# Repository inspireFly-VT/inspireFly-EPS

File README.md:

# inspireFly-EPS
inspireFly's custom EPS made for development of an open CubeSat architecture.

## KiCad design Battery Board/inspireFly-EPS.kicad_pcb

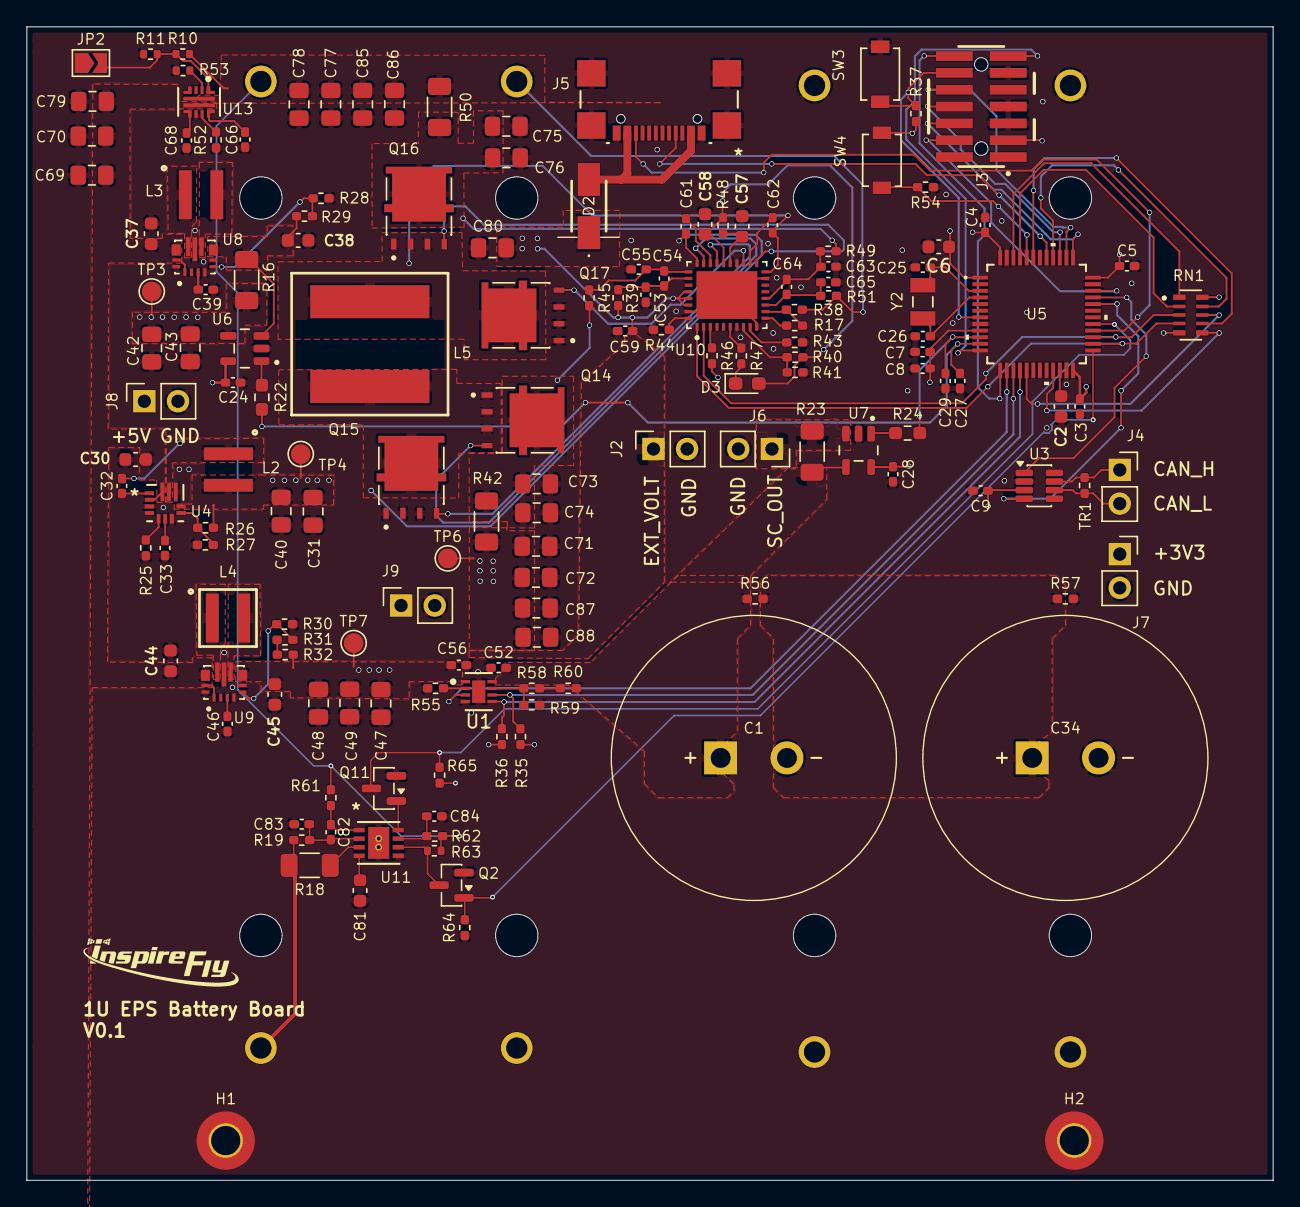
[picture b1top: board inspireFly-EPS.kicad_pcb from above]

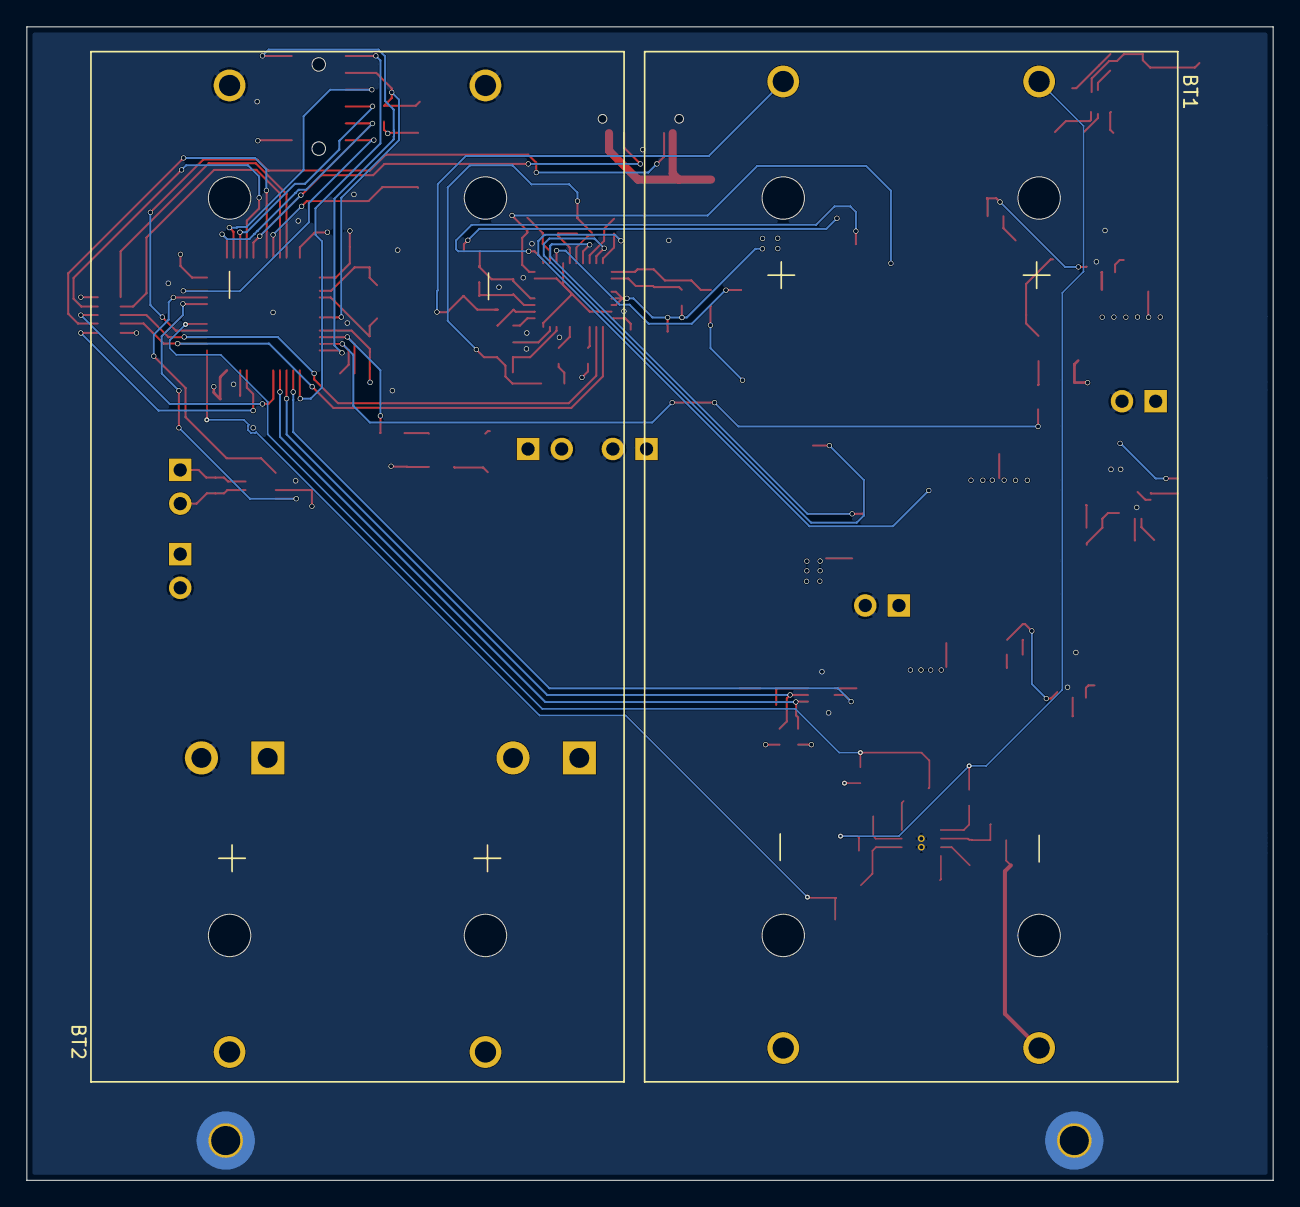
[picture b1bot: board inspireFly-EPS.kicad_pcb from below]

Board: 4 copper layers, 94.0 x 87.0 mm, 160 parts (2 on the bottom side), 100 nets.

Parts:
BT1, BT2: BK-18650-PC4; BAT_BK-18650-PC4
C1, C34: 1.5F; CH3R6155CF-ZJN
C2, C57, C58: 4.7uF; C_0603_1608Metric
C3, C4, C5, C8, C9, C24, C27, C28, C29, C39, C46, C53, C55, C61, C62, C63, C65, C82, C83, C84: 100nF; C_0402_1005Metric_Pad0.74x0.62mm_HandSolder
C6, C30, C37, C38, C44, C45: 10uF; C_0603_1608Metric
C7, C52, C56, C59: 1uF; C_0402_1005Metric_Pad0.74x0.62mm_HandSolder
C25, C26: 22pF; C_0402_1005Metric_Pad0.74x0.62mm_HandSolder
C31, C40, C42, C43, C47, C48, C49, C69, C70, C71, C72, C73, C74, C75, C76, C77, C78, C79, C80, C85, C86, C87, C88: 22uF; C_0805_2012Metric_Pad1.18x1.45mm_HandSolder
C32: 220nF; C_0402_1005Metric_Pad0.74x0.62mm_HandSolder
C33: 2.2uF; C_0402_1005Metric_Pad0.74x0.62mm_HandSolder
C54, C64: 470nF; C_0402_1005Metric_Pad0.74x0.62mm_HandSolder
C66, C68: 10nF; C_0402_1005Metric_Pad0.74x0.62mm_HandSolder
C81: 0.33uF; C_0603_1608Metric
D2: SDT5A60SA; SDT5A60SA13
D3: LTST-S270KRKT; LED_0603_1608Metric_Pad1.05x0.95mm_HandSolder
H1, H2: MountingHole_Pad; MountingHole_2.2mm_M2_Pad_TopBottom
J2, J4, J6, J7, J8, J9: Conn_01x02_Pin; PinSocket_1x02_P2.54mm_Vertical
J3: FTSH-107-01-L-DV-K-A; SAMTEC_FTSH-107-01-L-DV-K-A
J5: USB4110-GF-A; USB4110-GF-A_GCT
JP2: FTSW EN; SolderJumper-2_P1.3mm_Open_TrianglePad1.0x1.5mm
L2, L3: 1.5uH; WE-MAPI_4020
L4: 2.2uH; WE-MXGI_4020
L5: 10uH; WE-XHMA_1090
Q2, Q11: 2N7002; SOT-23
Q14, Q15, Q16, Q17: SQJA62EP-T1_GE3; TRANS_SQJA62EP-T1_GE3
R10, R53: 390k; R_0402_1005Metric
R11: 110k; R_0402_1005Metric
R16, R23, R42, R50: 5m; R_1206_3216Metric_Pad1.30x1.75mm_HandSolder
R17: 47k; R_0402_1005Metric_Pad0.72x0.64mm_HandSolder
R18: 442; R_1206_3216Metric_Pad1.30x1.75mm_HandSolder
R19, R61: 261; R_0402_1005Metric_Pad0.72x0.64mm_HandSolder
R22, R24: 10; R_0603_1608Metric_Pad0.98x0.95mm_HandSolder
R25: 115k; R_0402_1005Metric_Pad0.72x0.64mm_HandSolder
R26: 180k; R_0402_1005Metric_Pad0.72x0.64mm_HandSolder
R27, R28, R30, R44: 40k; R_0402_1005Metric_Pad0.72x0.64mm_HandSolder
R29, R31, R38: 210k; R_0402_1005Metric_Pad0.72x0.64mm_HandSolder
R32, R56, R57: 200k; R_0402_1005Metric_Pad0.72x0.64mm_HandSolder
R35, R36, R37, R46, R47, R65: 10k; R_0402_1005Metric_Pad0.72x0.64mm_HandSolder
R39, R45, R48, R49, R51: 10; R_0402_1005Metric_Pad0.72x0.64mm_HandSolder
R40: 6.2k; R_0402_1005Metric_Pad0.72x0.64mm_HandSolder
R41: 36k; R_0402_1005Metric_Pad0.72x0.64mm_HandSolder
R43: 15k; R_0402_1005Metric_Pad0.72x0.64mm_HandSolder
R52: 680; R_0402_1005Metric_Pad0.72x0.64mm_HandSolder
R54, R59, R64: 100k; R_0402_1005Metric_Pad0.72x0.64mm_HandSolder
R55: 12k; R_0402_1005Metric_Pad0.72x0.64mm_HandSolder
R58: 560k; R_0402_1005Metric_Pad0.72x0.64mm_HandSolder
R60: 240k; R_0402_1005Metric_Pad0.72x0.64mm_HandSolder
R62: 100; R_0402_1005Metric_Pad0.72x0.64mm_HandSolder
R63: 1M; R_0402_1005Metric
RN1: YC158TJR-072K2L; RESCAXE64P320X160X70-10N
SW3, SW4: SW_TL1015AF160QG
TP3: +5V; TestPoint_Pad_D1.5mm
TP4: +3V; TestPoint_Pad_D1.5mm
TP6: V_COMBINED; TestPoint_Pad_D1.5mm
TP7: +9V; TestPoint_Pad_D1.5mm
TR1: 120; R_0402_1005Metric_Pad0.72x0.64mm_HandSolder
U1: BQ25173DSGR; DSG0008A-IPC_B
U3: TCAN332DCNR; SOT-23-8
U4: MAX77504AAFC+T; 21-100406_F122A2F&plus_2_MXM
U5: STM32U575CIT6; LQFP48-7x7mm_STM
U6, U7: INA180A3IDBVT; SOT95P280X145-5N
U8, U9: TPS63070RNMR; VREG_TPS63070RNMR
U10: BQ25756ERRVR; IC_BQ25756ERRVR
U11: BQ29209DRBR; DRB8_1P6X2P4
U13: TPS259472ARPWR; RPW0010A-MFG
Y2: XTAL_ABS07-32.768KHZ-T

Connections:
+3.3V: C3.1, C4.1, C5.1, C6.1, C7.1, C8.1, C9.1, C24.1, C28.1, C31.2, C40.2, J3.03, J7.1, L2.2, R26.2, R35.1, R36.1, R37.1, R46.2, R65.2, RN1.5, RN1.10, SW4.2, TP4.1 (1_1), U3.3 (VCC), U4.9 (OUT), U5.1 (VBAT), U5.9 (VDDA), U5.24 (VDD), U5.36 (VDD), U5.48 (VDD), U6.5 (VS), U7.5 (VS)
+5V: C42.2, C43.2, J8.1, R16.2, TP3.1 (1_1), U6.4 (IN-)
+9V: C45.1, C47.2, C48.2, C49.2, C56.2, J9.1, R32.2, TP7.1 (1_1), U1.1 (IN), U9.7_8 (VOUT)
ACN: C54.2, C55.2, R45.1, U10.29 (ACN)
ACP: C53.1, C54.1, R39.1, U10.30 (ACP)
ADC1_IN3: C29.1, R24.2, U5.10 (PA0)
ADC1_IN4: C27.1, R22.2, U5.11 (PA1)
BAL_EN: Q2.1 (G), R64.2, U5.25 (PB12)
BAT+: BT1.1+, BT1.2+, C77.1, C78.1, C85.1, C86.1, R10.2, R38.2, R50.2, R51.2, R61.2, R62.2, R63.2, U13.5 (IN)
BATMANG_INT_DIN: R46.1, U10.3 (~INT)
BAT_HIGH_SIDE_DRIVE: Q16.2 (G), U10.19 (HIDRV2)
BAT_LOW_SIDE_DRIVE: Q17.2 (G), U10.21 (LODRV2)
BAT_SIDE_INDUC: C62.1, L5.2, Q16.3 (S), Q17.1 (D), U10.18 (SW2)
BOOT0: R54.2, SW4.1, U5.44 (PH3-BOOT0)
CAN_H: J4.1, TR1.1, U3.7 (CANH)
CAN_L: J4.2, TR1.2, U3.6 (CANL)
CAN_RXD: U3.4 (RXD), U5.32 (PA11)
CAN_TXD: U3.1 (TXD), U5.33 (PA12)
CELL_MID: BT1.1-, BT1.2-, BT2.1+, BT2.2+, R18.2, R19.2
CELL_OVP_N: Q11.3 (D), R65.1, U5.29 (PA8)
DEBUG_LPUART_RX: J3.14, U5.13 (PA3)
DEBUG_LPUART_TX: J3.13, U5.12 (PA2)
EXTERNAL_HIGH_SIDE_DRIVE: Q14.2 (G), U10.27 (HIDRV1)
EXTERNAL_LOW_SIDE_DRIVE: Q15.2 (G), U10.25 (LODRV1)
EXTERNAL_SIDE_INDUC: C61.1, L5.1, Q14.3 (S), Q15.1 (D), U10.28 (SW1)
EXTERNAL_VOLTAGE: C59.2, C71.1, C72.1, C80.1, C87.1, C88.1, D2.1 (K), J2.1, R39.2, R42.1, TP6.1 (1_1), U10.32 (VAC), U10.33 (VAC__1), U10.34 (ACUV)
GND: BT2.1-, BT2.2-, C2.2, C3.2, C4.2, C5.2, C6.2, C7.2, C8.2, C9.2, C24.2, C25.1, C26.1, C27.2, C28.2, C29.2, C30.2, C31.1, C33.1, C34.2, C37.2, C38.2, C39.2, C40.1, C42.1, C43.1, C44.2, C45.2, C46.2, C47.1, C48.1, C49.1, C52.1, C53.2, C55.1, C56.1, C57.2, C58.2, C59.1, C63.2, C65.1, C66.1, C68.1, C69.2, C70.2, C71.2, C72.2, C73.2, C74.2, C75.2, C76.2, C77.2, C78.2, C79.2, C80.2, C81.1, C83.1, C84.1, C85.2, C86.2, C87.2, C88.2, H1.1 (1_1), H2.1 (1_1), J2.2, J3.05, J3.07, J3.11, J5.15 (Shield), J5.16 (Shield), J5.17 (Shield), J5.18 (Shield), J5.A1-B12 (GND), J5.A12-B1 (GND), J6.2, J7.2, J8.2, J9.2, Q2.2 (S), Q11.2 (S), Q15.3 (S), Q17.3 (S), R11.1, R25.1, R27.1, R28.2, R30.2, R41.2, R43.2, R44.1, R52.1, R53.2, R54.1, R55.2, R57.2, R59.2, R64.1, SW3.2, U1.4 (GND), U1.9 (Thermal_Pad), U3.2 (GND), U4.3 (FPWM/SYNC), U4.7 (AGND), U4.10 (PGND), U5.8 (VSSA), U5.23 (VSS), U5.35 (VSS), U5.47 (VSS), U6.2 (GND), U7.2 (GND), U8.4 (GND), U8.6 (FB2), U8.10 (PGND), U8.15 (VSEL), U9.4 (GND), U9.6 (FB2), U9.10 (PGND), U9.15 (VSEL), U10.7 (~CE), U10.10 (ILIM_HIZ), U10.17 (PGND), U10.22 (PGND__1), U10.35 (ACOV), U10.37 (PGND__2), U11.5 (GND), U11.9 (EPAD), U13.8 (GND)
I2C1_SCL: RN1.2, U5.45 (PB8)
I2C1_SDA: RN1.1, U5.46 (PB9)
I2C2_SCL: RN1.4, U5.26 (PB13), U10.1 (SCL)
I2C2_SDA: RN1.3, U5.27 (PB14), U10.2 (SDA)
I2C3_SCL: RN1.8, U5.17 (PA7)
I2C3_SDA: RN1.9, U5.40 (PB4)
I2C4_SCL: RN1.6, U5.21 (PB10)
I2C4_SDA: RN1.7, U5.43 (PB7)
JTCK/SWCLK: J3.06, U5.37 (PA14)
JTDI: J3.10, U5.38 (PA15)
JTMS/SWDIO: J3.04, U5.34 (PA13)
NRST: J3.12, R37.2, SW3.1, U5.7 (NRST)
unnamed: C1.2, C34.1, R56.2, R57.1
unnamed: D3.1 (K), R47.1
unnamed: JP2.2 (B), R10.1, R11.2, U13.1 (EN_UVLO)
unnamed: Q2.3 (D), R63.1, U11.6 (*CB_EN)
unnamed: Q11.1 (G), U11.8 (OUT)
unnamed: C73.1, C74.1, Q14.1 (D), R42.2, R45.2
unnamed: C75.1, C76.1, Q16.1 (D), R49.2, R50.1
unnamed: R31.1, R32.1
unnamed: R58.2, R60.2
unnamed: R58.1, R59.1, U1.7 (FB)
unnamed: R55.1, U1.2 (ISET)
unnamed: C32.2, U4.1 (BST)
unnamed: R26.1, R27.2, U4.8 (FB)
unnamed: C32.1, L2.1, U4.11 (LX)
unnamed: R25.2, U4.5 (SEL)
unnamed: C33.2, U4.6 (VL)
unnamed: C25.2, U5.3 (PC14-OSC32_IN), Y2.1
unnamed: C26.2, U5.4 (PC15-OSC32_OUT), Y2.2
unnamed: C2.1, U5.22 (VCAP)
unnamed: C38.1, R16.1, R29.1, U6.3 (IN+), U8.7_8 (VOUT)
unnamed: R22.1, U6.1 (OUT)
unnamed: R24.1, U7.1 (OUT)
unnamed: R28.1, R29.2, U8.5 (FB)
unnamed: L3.1, U8.11 (L1)
unnamed: L3.2, U8.9 (L2)
unnamed: C39.1, U8.3 (VAUX)
unnamed: R30.1, R31.2, U9.5 (FB)
unnamed: L4.1, U9.11 (L1)
unnamed: L4.2, U9.9 (L2)
unnamed: C46.1, U9.3 (VAUX)
unnamed: C61.2, U10.26 (BTST1)
unnamed: C62.2, U10.20 (BTST2)
unnamed: C57.1, R48.1, U10.23 (DRV_SUP)
unnamed: R17.2, R38.1, U10.12 (FB)
unnamed: R17.1, U10.11 (FBG)
unnamed: R44.2, U10.36 (FSW_SYNC)
unnamed: R43.1, U10.9 (ICHG)
unnamed: R47.2, U10.6 (~PG)
unnamed: C81.2, U11.4 (CD)
unnamed: C82.1, C83.2, R19.1, U11.2 (VC1)
unnamed: R18.1, U11.3 (VC1_CB)
unnamed: C82.2, R61.1, U11.1 (VC2)
unnamed: C84.2, R62.1, U11.7 (VDD)
unnamed: R52.2, U13.9 (ILM)
unnamed: C66.2, U13.10 (ITIMER)
unnamed: R53.1, U13.2 (OVCSEL)
unnamed: C68.2, U13.7 (dVdt)
PROTECTED_VOLTAGE: C30.1, C37.1, C44.1, C69.1, C70.1, C79.1, U4.2 (EN), U4.12 (SUP), U8.1 (PS/SYNC), U8.12_13 (VIN), U8.14 (EN), U9.1 (PS/SYNC), U9.12_13 (VIN), U9.14 (EN), U13.6 (OUT)
REGN: C58.1, D3.2 (A), R40.1, R48.2, U10.24 (REGN)
SRN: C64.2, C65.2, R51.1, U10.13 (SRN)
SRP: C63.1, C64.1, R49.1, U10.14 (SRP)
SUPERCAP_CE: U1.3 (CE_N), U5.14 (PA4)
SUPERCAP_LOAD/SLOWCHARGE: C1.1, C52.2, R23.2, R56.1, R60.1, U1.8 (OUT), U7.4 (IN-)
SUPERCAP_OUT: J6.1, R23.1, U7.3 (IN+)
SUPERCAP_PG: R35.2, U1.6 (PG_N), U5.15 (PA5)
SUPERCAP_STAT: R36.2, U1.5 (STAT), U5.16 (PA6)
SWO: J3.08, U5.39 (PB3)
THERMISTOR_FEEDBACK: R40.2, R41.1, U10.8 (TS)
USB_CC1: J5.A5 (CC1), U5.41 (PB5)
USB_CC2: J5.B5 (CC2), U5.28 (PB15)
USB_V: D2.2 (A), J5.A4-B9 (VBUS), J5.A9-B4 (VBUS)

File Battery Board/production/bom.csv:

Designator,Footprint,Quantity,Value,LCSC Part #
"BT1, BT2",BAT_BK-18650-PC4,2,BK-18650-PC4,
"C1, C34",CH3R6155CF-ZJN,2,1.5F,
"C2, C57, C58",0603,3,4.7uF,
"C24, C27, C28, C29, C3, C39, C4, C46, C5, C53, C55, C61, C62, C63, C65, C8, C82, C83, C84, C9",0402,20,100nF,
"C25, C26",0402,2,22pF,
"C30, C37, C38, C44, C45, C6",0603,6,10uF,
"C31, C40, C42, C43, C47, C48, C49, C69, C70, C71, C72, C73, C74, C75, C76, C77, C78, C79, C80, C85, C86, C87, C88",0805,23,22uF,
C32,0402,1,220nF,
C33,0402,1,2.2uF,
"C52, C56, C59, C7",0402,4,1uF,
"C54, C64",0402,2,470nF,
"C66, C68",0402,2,10nF,
C81,0603,1,0.33uF,
D2,SDT5A60SA13,1,SDT5A60SA,
D3,0603,1,LTST-S270KRKT,
"J2, J4, J6, J7, J8, J9",PinSocket_1x02_P2.54mm_Vertical,6,Conn_01x02_Pin,
J3,SAMTEC_FTSH-107-01-L-DV-K-A,1,FTSH-107-01-L-DV-K-A,
J5,USB4110-GF-A_GCT,1,USB4110-GF-A,
JP2,SolderJumper-2_P1.3mm_Open_TrianglePad1.0x1.5mm,1,FTSW EN,
"L2, L3",WE-MAPI_4020,2,1.5uH,
L4,WE-MXGI_4020,1,2.2uH,
L5,WE-XHMA_1090,1,10uH,
"Q11, Q2",SOT-23,2,2N7002,
"Q14, Q15, Q16, Q17",TRANS_SQJA62EP-T1_GE3,4,SQJA62EP-T1_GE3,
"R10, R53",0402,2,390k,
R11,0402,1,110k,
"R16, R23, R42, R50",1206,4,5m,
R17,0402,1,47k,
R18,1206,1,442,
"R19, R61",0402,2,261,
"R22, R24",0603,2,10,
R25,0402,1,115k,
R26,0402,1,180k,
"R27, R28, R30, R44",0402,4,40k,
"R29, R31, R38",0402,3,210k,
"R32, R56, R57",0402,3,200k,
"R35, R36, R37, R46, R47, R65",0402,6,10k,
"R39, R45, R48, R49, R51",0402,5,10,
R40,0402,1,6.2k,
R41,0402,1,36k,
R43,0402,1,15k,
R52,0402,1,680,
"R54, R59, R64",0402,3,100k,
R55,0402,1,12k,
R58,0402,1,560k,
R60,0402,1,240k,
R62,0402,1,100,
R63,0402,1,1M,
RN1,RESCAXE64P320X160X70-10N,1,YC158TJR-072K2L,
"SW3, SW4",SW_TL1015AF160QG,2,SW_TL1015AF160QG,
TP3,TestPoint_Pad_D1.5mm,1,+5V,
TP4,TestPoint_Pad_D1.5mm,1,+3V,
TP6,TestPoint_Pad_D1.5mm,1,V_COMBINED,
TP7,TestPoint_Pad_D1.5mm,1,+9V,
TR1,0402,1,120,
U1,DSG0008A-IPC_B,1,BQ25173DSGR,
U10,IC_BQ25756ERRVR,1,BQ25756ERRVR,
U11,DRB8_1P6X2P4,1,BQ29209DRBR,
U13,RPW0010A-MFG,1,TPS259472ARPWR,
U3,SOT-23-8,1,TCAN332DCNR,
U4,21-100406_F122A2F&plus_2_MXM,1,MAX77504AAFC+T,
U5,LQFP48-7x7mm_STM,1,STM32U575CIT6,
"U6, U7",SOT95P280X145-5N,2,INA180A3IDBVT,
"U8, U9",VREG_TPS63070RNMR,2,TPS63070RNMR,
Y2,XTAL_ABS07-32.768KHZ-T,1,XTAL_ABS07-32.768KHZ-T,

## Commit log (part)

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2025-05-07 Updated with USB-C - should be finished
2025-05-08 Good progress on BQ chip - need to do math later
2025-05-10 Changes to BQ Chip
    Calculated some values, see overleaf doc. Adjusted presentation on schematic in regards to BQ chip. Also added battery holders
2025-05-18 More BQ work
2025-06-01 Updates to BQ chip and routing
2025-06-07 reroute of BQ chip
2025-06-07 Placed STM chip
2025-06-08 routed usb c
2025-06-12 Added diode to USB
2025-06-14 Added INAs
2025-06-15 Slight Routing updates
2025-07-01 added 3.3V to schematic
2025-07-06 Schematic additions, some routing changes
2025-07-06 Routing fixes
2025-07-13 Fixed mistake on 3.3V reg
2025-07-20 Lots of routing
2025-07-24 Updated STM location
2025-07-28 Added Dead battery to BQ and other routing changes
2025-08-04 About ready for proto 1
2025-08-10 routing updates
2025-09-28 Adding Lock File + Ruleset
2025-10-13 Adding 3D file
2026-02-18 Add files via upload
    Supercapacitor Array Excel Sheet
2026-03-03 Updated the ST575 to have a 14 pin debugger
    Routed and added to schematic.
2026-03-22 Routing and STLink debugger.
2026-03-29 Schematic rework
2026-03-29 Schematic Updates
2026-03-30 3.3V routing changes
2026-04-01 Pushing routing changes, finailize vreg locations
2026-04-19 Added linear charger to schematic
2026-04-26 Routed all capacitors
2026-04-26 Finished Linear Charger Schematic
2026-04-26 Added 3D step file to linear charger
2026-04-26 Added 3D step files
